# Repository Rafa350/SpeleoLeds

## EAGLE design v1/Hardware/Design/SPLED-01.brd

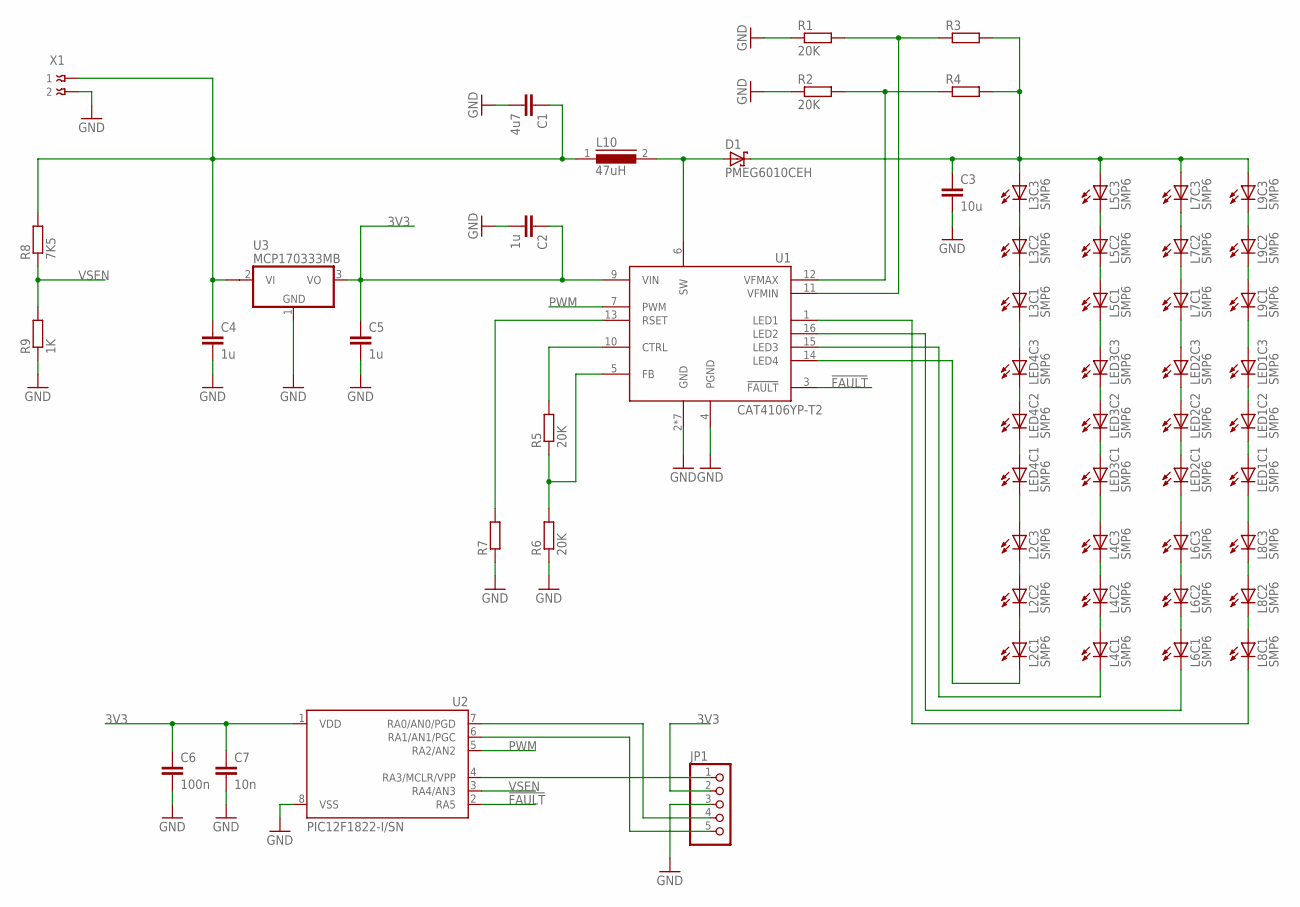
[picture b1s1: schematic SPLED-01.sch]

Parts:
C1: 4u7; C1206K
C2, C4, C5: 1u; C1206K
C3: 10u; C1206K
C6: 100n; C1206K
C7: 10n; C1206K
D1: PMEG6010CEH; SOD123FL
JP1: PINHD-1X5-2MM; 1X05-2MM
L2, L3, L4, L5, L6, L7, L8, L9: SMP6; PLCC6
L10: 47uH; DR73
LED1, LED2, LED3, LED4: SMP6; PLCC6
R1, R2, R5, R6: 20K; R1206
R3, R4, R7: R-EU_R1206; R1206
R8: 7K5; R1206
R9: 1K; R1206
U1: CAT4106YP-T2; TSSOP16
U2: PIC12F1822-I/SN; SO08
U3: MCP170333MB; SOT89
X1: 009176002

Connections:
3V3: C2.1, C5.1, C6.1, C7.1, JP1.2, U1.9 (VIN), U2.1 (VDD), U3.3 (VO)
!FAULT!: U1.3 (!FAULT!), U2.2 (RA5)
GND: C1.2, C2.2, C3.2, C4.2, C5.2, C6.2, C7.2, JP1.3, R1.1, R2.1, R6.1, R7.1, R9.1, U1.2 (GND), U1.4 (PGND), U1.P$1 (GND), U1.P$2 (GND), U1.P$3 (GND), U1.P$4 (GND), U1.P$5 (GND), U1.P$6 (GND), U2.8 (VSS), U3.1 (GND), X1.2
unnamed: D1.A, L10.2, U1.6 (SW)
unnamed: L3.4 (A), L3.5 (C)
unnamed: L3.2 (A), L3.3 (C)
unnamed: L3.1 (C), LED4.6 (A)
unnamed: L2.4 (A), L2.5 (C)
unnamed: L2.2 (A), L2.3 (C)
unnamed: L5.4 (A), L5.5 (C)
unnamed: L5.2 (A), L5.3 (C)
unnamed: L5.1 (C), LED3.6 (A)
unnamed: L4.4 (A), L4.5 (C)
unnamed: L4.2 (A), L4.3 (C)
unnamed: L6.2 (A), L6.3 (C)
unnamed: L6.4 (A), L6.5 (C)
unnamed: L7.1 (C), LED2.6 (A)
unnamed: L7.2 (A), L7.3 (C)
unnamed: L7.4 (A), L7.5 (C)
unnamed: L9.4 (A), L9.5 (C)
unnamed: L9.2 (A), L9.3 (C)
unnamed: L9.1 (C), LED1.6 (A)
unnamed: L8.4 (A), L8.5 (C)
unnamed: L8.2 (A), L8.3 (C)
unnamed: C3.1, D1.C, L3.6 (A), L5.6 (A), L7.6 (A), L9.6 (A), R3.2, R4.2
unnamed: L2.1 (C), U1.14 (LED4)
unnamed: L4.1 (C), U1.15 (LED3)
unnamed: L6.1 (C), U1.16 (LED2)
unnamed: L8.1 (C), U1.1 (LED1)
unnamed: LED1.4 (A), LED1.5 (C)
unnamed: LED1.2 (A), LED1.3 (C)
unnamed: R5.2, U1.10 (CTRL)
unnamed: R2.2, R4.1, U1.12 (VFMAX)
unnamed: R1.2, R3.1, U1.11 (VFMIN)
unnamed: L8.6 (A), LED1.1 (C)
unnamed: L6.6 (A), LED2.1 (C)
unnamed: R5.1, R6.2, U1.5 (FB)
unnamed: LED2.2 (A), LED2.3 (C)
unnamed: R7.2, U1.13 (RSET)
unnamed: LED2.4 (A), LED2.5 (C)
unnamed: LED3.4 (A), LED3.5 (C)
unnamed: LED3.2 (A), LED3.3 (C)
unnamed: L4.6 (A), LED3.1 (C)
unnamed: L2.6 (A), LED4.1 (C)
unnamed: LED4.2 (A), LED4.3 (C)
unnamed: LED4.4 (A), LED4.5 (C)
PGC: JP1.5, U2.6 (RA1/AN1/PGC)
PGD: JP1.4, U2.7 (RA0/AN0/PGD)
PWM: U1.7 (PWM), U2.5 (RA2/AN2)
VBAT: C1.1, C4.1, L10.1, R8.2, U3.2@1 (VI1), X1.1
VPP: JP1.1, U2.4 (RA3/MCLR/VPP)
VSEN: R8.1, R9.2, U2.3 (RA4/AN3)

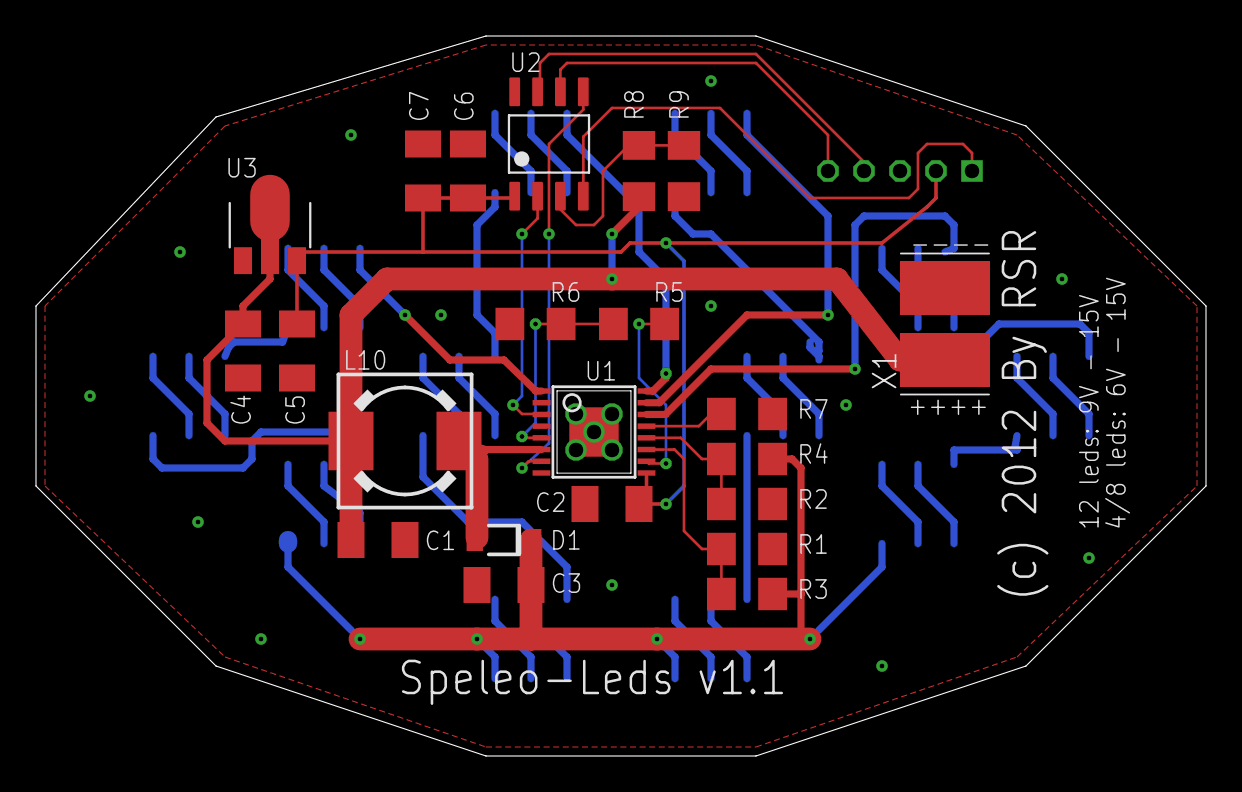
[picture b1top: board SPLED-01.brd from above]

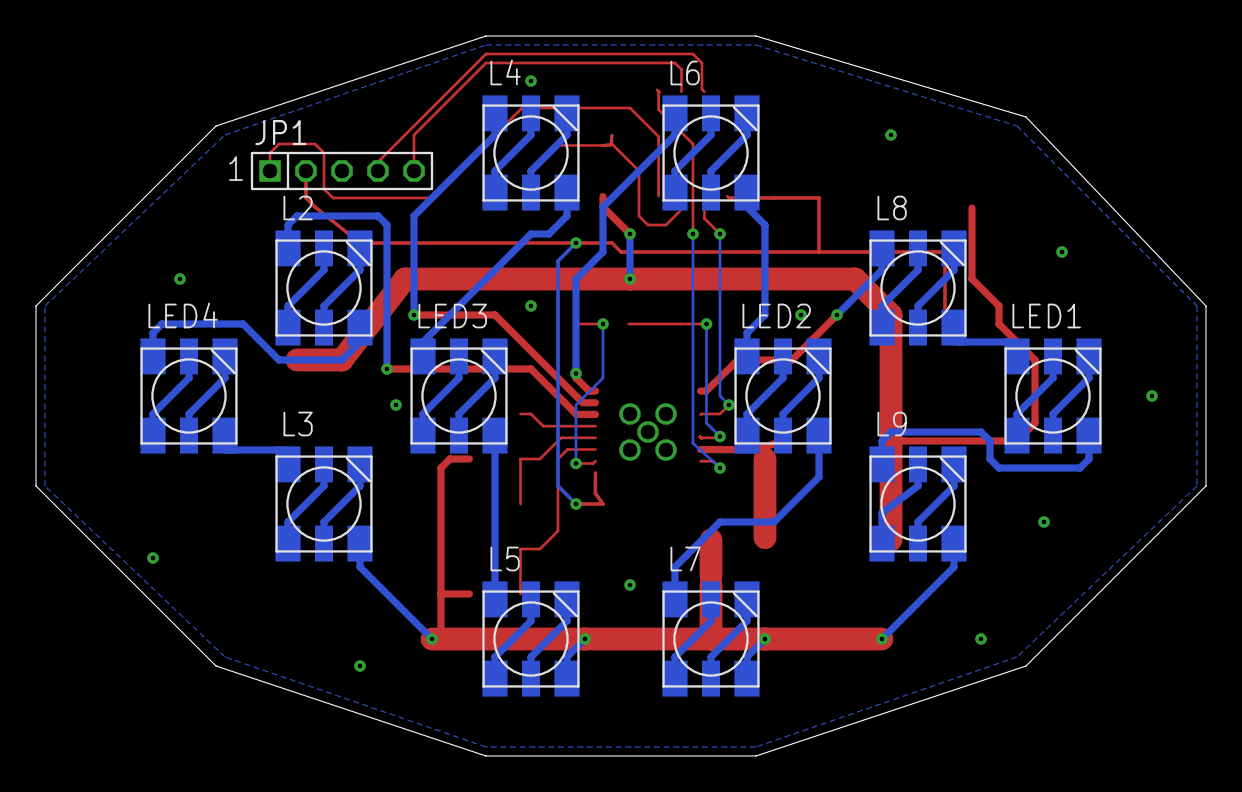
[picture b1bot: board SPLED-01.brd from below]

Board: 2 copper layers, 65.0 x 40.0 mm, 35 parts (13 on the bottom side), 52 nets.

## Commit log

2016-02-12 :octocat: Added .gitattributes
2016-02-12 readme.md added
2016-02-12 Added documentation files
2016-02-12 Added datasheets for microcontroller, leds, and driver
2016-02-12 Added more files of v1
    Datasheets, schematic and board, and photos of first version
2016-02-12 Added images of version 2

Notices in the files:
v1/Hardware/Design/SPLED-01.brd:
(c) 2012 By RSR
